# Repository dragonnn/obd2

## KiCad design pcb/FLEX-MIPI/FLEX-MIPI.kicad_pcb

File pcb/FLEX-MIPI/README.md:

# OK-23GF030-04 KiCad library

KiCad symbol, PCB footprint, and simplified STEP model for the 30-pin OCN
`OK-23GF030-04` board-side receptacle. This mates with the
`OK-23GM030-04` plug specified by the Osptek AM319M262928ZS panel drawing.

## Files

- `OK-23GF030-04.kicad_sym` — generic 30-pin connector symbol
- `OK-23GF030-04.pretty/CONN-SMD_30P-OK-23GF030-04.kicad_mod` — 0.4 mm-pitch footprint
- `OK-23GF030-04.3dshapes/CONN-SMD_30P-OK-23GF030-04.step` — simplified STEP model
- `OK-23GF030-04.3dshapes/CONN-SMD_30P-OK-23GF030-04.wrl` — EasyEDA-converted VRML model
- `generate_step.py` — CadQuery source for the STEP model

## Provenance and cautions

The symbol and land pattern were converted from JLCPCB/EasyEDA component
`C9900040133`. The four solder hold-down pads were changed from electrical
pin 0 to unnumbered mechanical pads, and the false pin 0 was removed from
the symbol.

The STEP model is an envelope/placement model aligned to that land pattern.
Its overall envelope is approximately 9.10 x 2.91 x 0.65 mm, including the
solder fittings. It is not manufacturer CAD;
small housing, latch, and mating-interface details are simplified. Confirm
the production footprint, component height, panel engagement, and keep-out
against physical samples or an OCN mechanical drawing before fabrication.

Do not substitute the earlier 24-pin `OK-14F024-04` footprint. It is a
different connector family and pin count.

## KiCad setup

Keep the `ok23_connector` folder at the project root so the footprint's
`${KIPRJMOD}` STEP path resolves. Add `OK-23GF030-04.kicad_sym` through
Preferences -> Manage Symbol Libraries, and add the `.pretty` directory
through Preferences -> Manage Footprint Libraries. Use the nickname
`OK-23GF030-04` for the footprint library.

For JLCPCB assembly, use LCSC/JLCPCB part `C9900040133` and verify current
stock and assembly orientation when ordering.

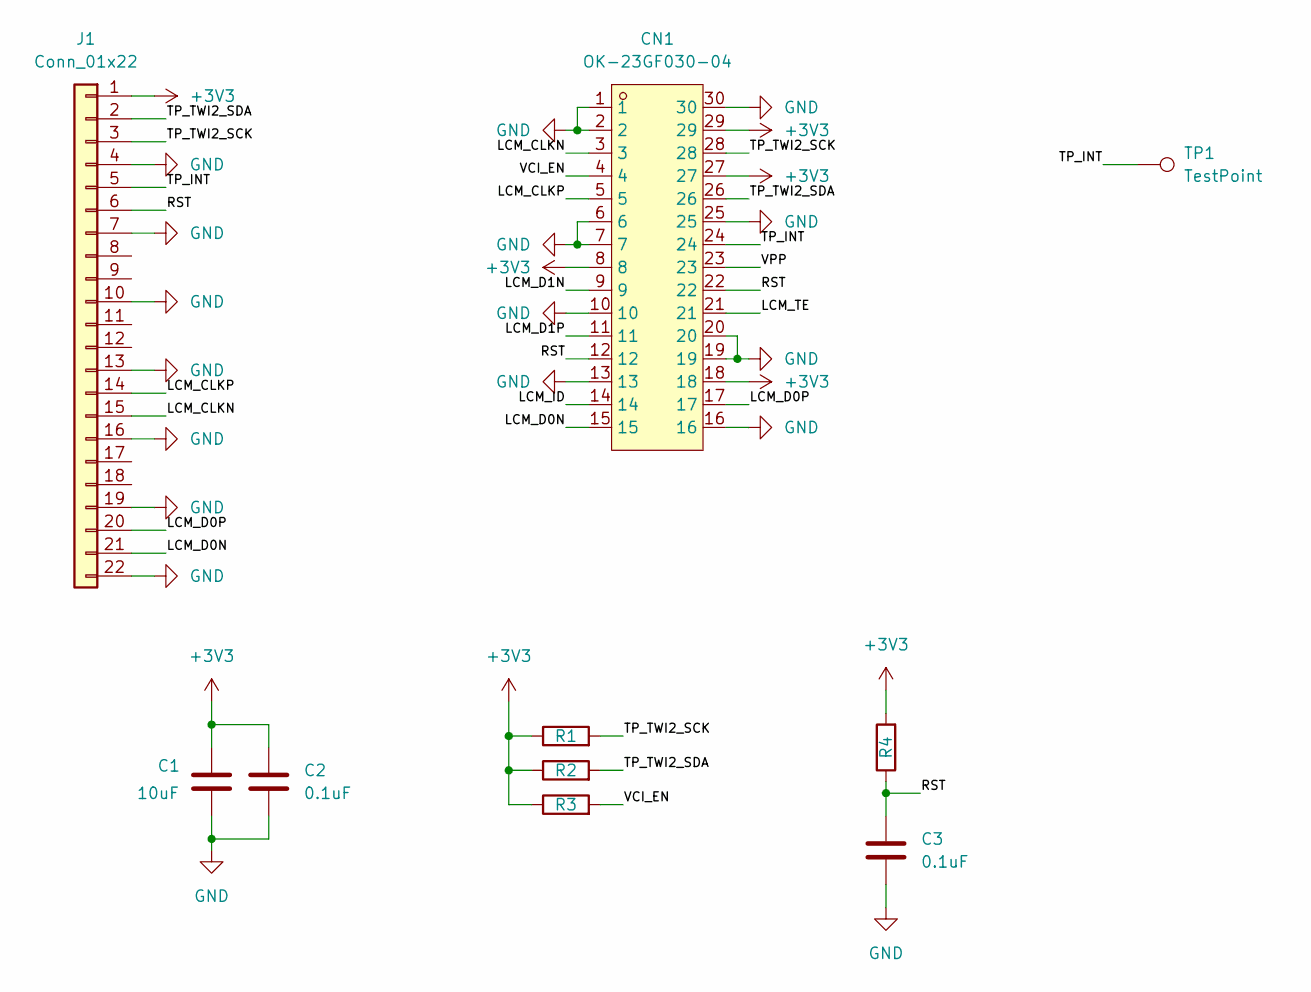
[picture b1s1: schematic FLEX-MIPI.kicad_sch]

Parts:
C1: 10uF; C_0805_2012Metric_Pad1.18x1.45mm_HandSolder
C2, C3: 0.1uF; C_0201_0603Metric_Pad0.64x0.40mm_HandSolder
CN1: OK-23GF030-04; CONN-SMD_30P-OK-23GF030-04; MPN OK-23GF030-04; LCSC Part C9900040133
J1: Conn_01x22; FPC_Tail_22P_P0.5
R1, R2, R3, R4: R; R_0201_0603Metric_Pad0.64x0.40mm_HandSolder
TP1: TestPoint; TestPoint_SMD_1.0x0.6mm_Flex

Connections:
+3V3: C1.1, C2.1, CN1.8, CN1.18, CN1.27, CN1.29, J1.1, R1.1, R2.1, R3.1, R4.2
/LCM_CLKN: CN1.3, J1.15
/LCM_CLKP: CN1.5, J1.14
/LCM_D0N: CN1.15, J1.21
/LCM_D0P: CN1.17, J1.20
/LCM_D1N: CN1.9
/LCM_D1P: CN1.11
/LCM_ID: CN1.14
/LCM_TE: CN1.21
/RST: C3.1, CN1.12, CN1.22, J1.6, R4.1
/TP_INT: CN1.24, J1.5, TP1.1
/TP_TWI2_SCK: CN1.28, J1.3, R1.2
/TP_TWI2_SDA: CN1.26, J1.2, R2.2
/VCI_EN: CN1.4, R3.2
/VPP: CN1.23
GND: C1.2, C2.2, C3.2, CN1.1, CN1.2, CN1.6, CN1.7, CN1.10, CN1.13, CN1.16, CN1.19, CN1.20, CN1.25, CN1.30, J1.4, J1.7, J1.10, J1.13, J1.16, J1.19, J1.22

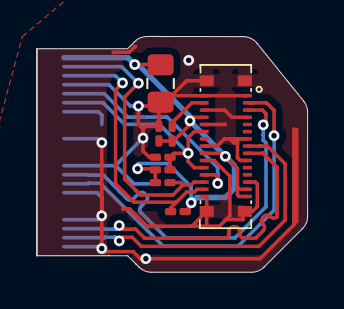
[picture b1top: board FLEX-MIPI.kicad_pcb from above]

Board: 2 copper layers, 15.0 x 13.0 mm, 9 parts (1 on the bottom side), 11 nets.

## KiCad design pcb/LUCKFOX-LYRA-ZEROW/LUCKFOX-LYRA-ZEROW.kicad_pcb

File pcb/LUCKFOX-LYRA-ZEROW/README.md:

# Luckfox Lyra Zero W — KiCad library

Contents:
- `Luckfox_Lyra.kicad_sym` — 40-pin symbol with 5V / 3V3 / GND and RMIO/GPIO names.
- `Luckfox_Lyra.pretty/Luckfox_Lyra_Zero_W_40Pin.kicad_mod` — footprint.
- `Luckfox_Lyra.3dshapes/Luckfox_Lyra_Zero_W.step` — simplified generated STEP model.

## Footprint philosophy
The footprint intentionally has **no F.SilkS board drawing**. The only PCB fabrication geometry is the 2×20 through-hole connector. The SBC board outline, four mounting holes, and mechanical notes are on `Cmts.User` so they are visible while laying out the carrier but do not print on silkscreen.

Board envelope: 65.0 × 30.0 mm. Mounting pattern: 58 × 23 mm, four Ø3.0 mm holes.

The 40-pin expansion connector uses 2.54 mm pitch. Pin 1 is the square pad. Pin numbering follows Raspberry-Pi-style alternating numbering: odd pins on the inner row, even pins on the outer/board-edge row.

## 3D model
Luckfox's documentation repository states that hardware resources include a `Hardware/3D Models/` directory, but an exact official Lyra Zero W STEP file was not available through the public indexed resources used while creating this package. Therefore the included STEP is generated from the published 65 × 30 mm board envelope and mounting geometry. It includes approximate major component envelopes and a generic installed 2×20 header for mechanical visualization. **Do not use component positions/heights from this STEP for a tight enclosure without measuring the real board.**

## Electrical pin mapping
RMIO/GPIO labels were transcribed from the official Luckfox Lyra Zero W schematic.

## Mechanical assumptions
The header and mounting-hole coordinates use the Raspberry Pi Zero-compatible 65 × 30 mm / 58 × 23 mm mechanical convention, consistent with Luckfox's stated Pi-HAT compatibility and published outline. If your carrier has very tight registration requirements, verify pin-1-to-board-edge dimensions against a physical Lyra Zero W before production.

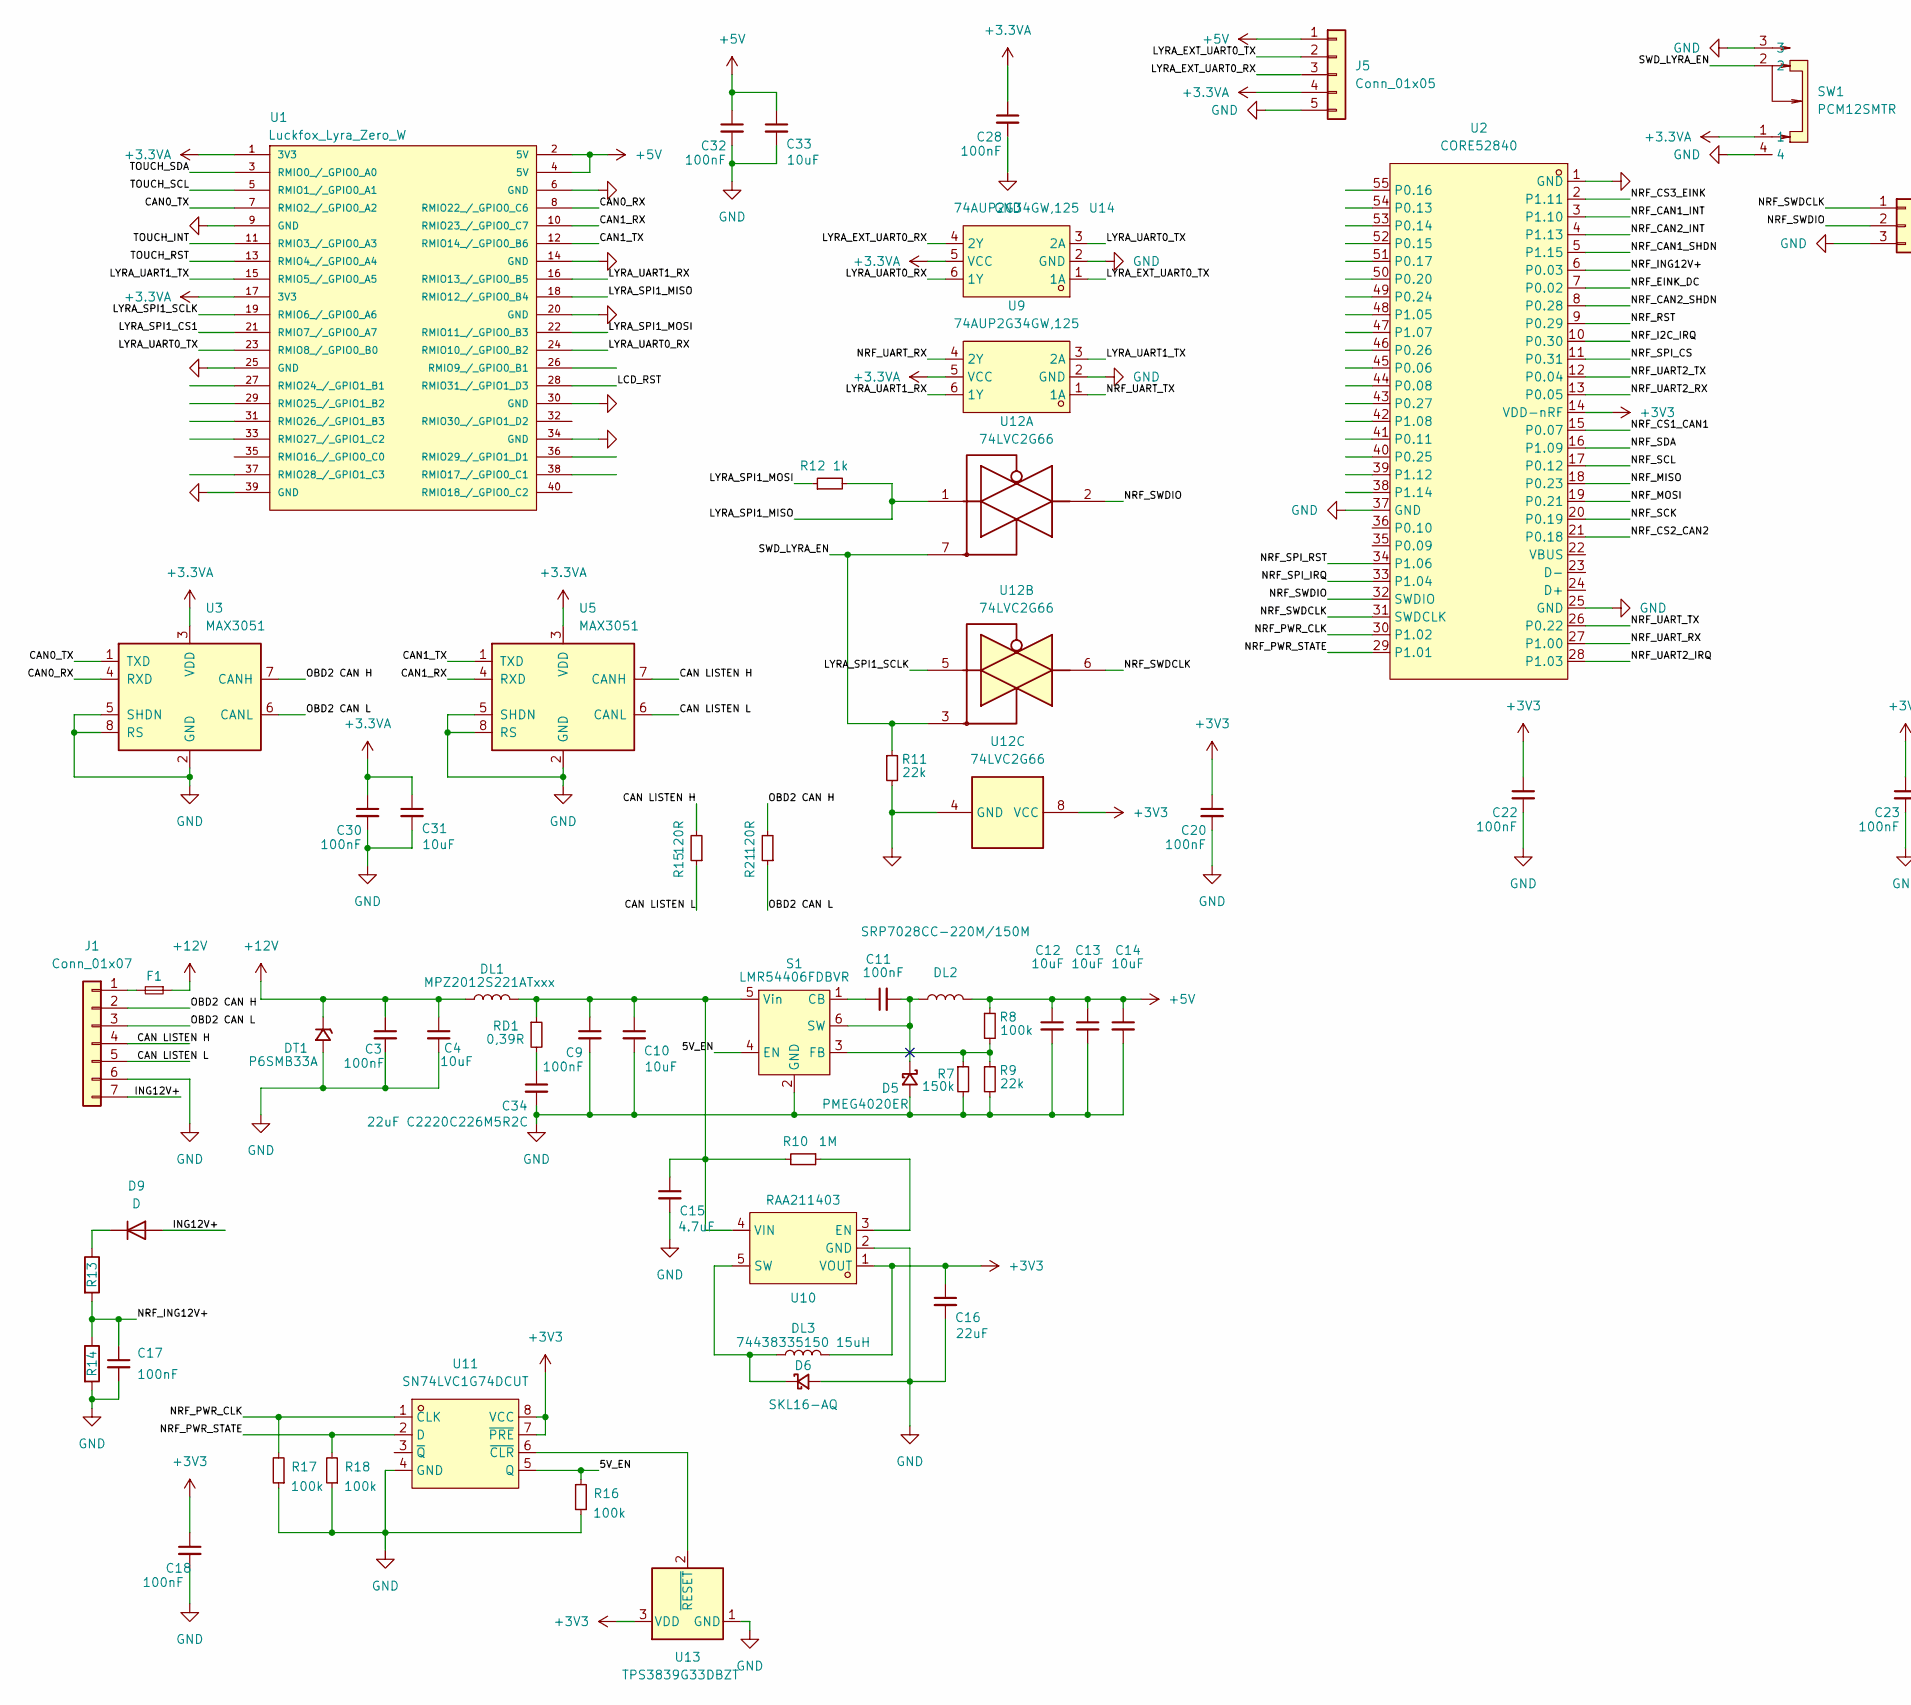
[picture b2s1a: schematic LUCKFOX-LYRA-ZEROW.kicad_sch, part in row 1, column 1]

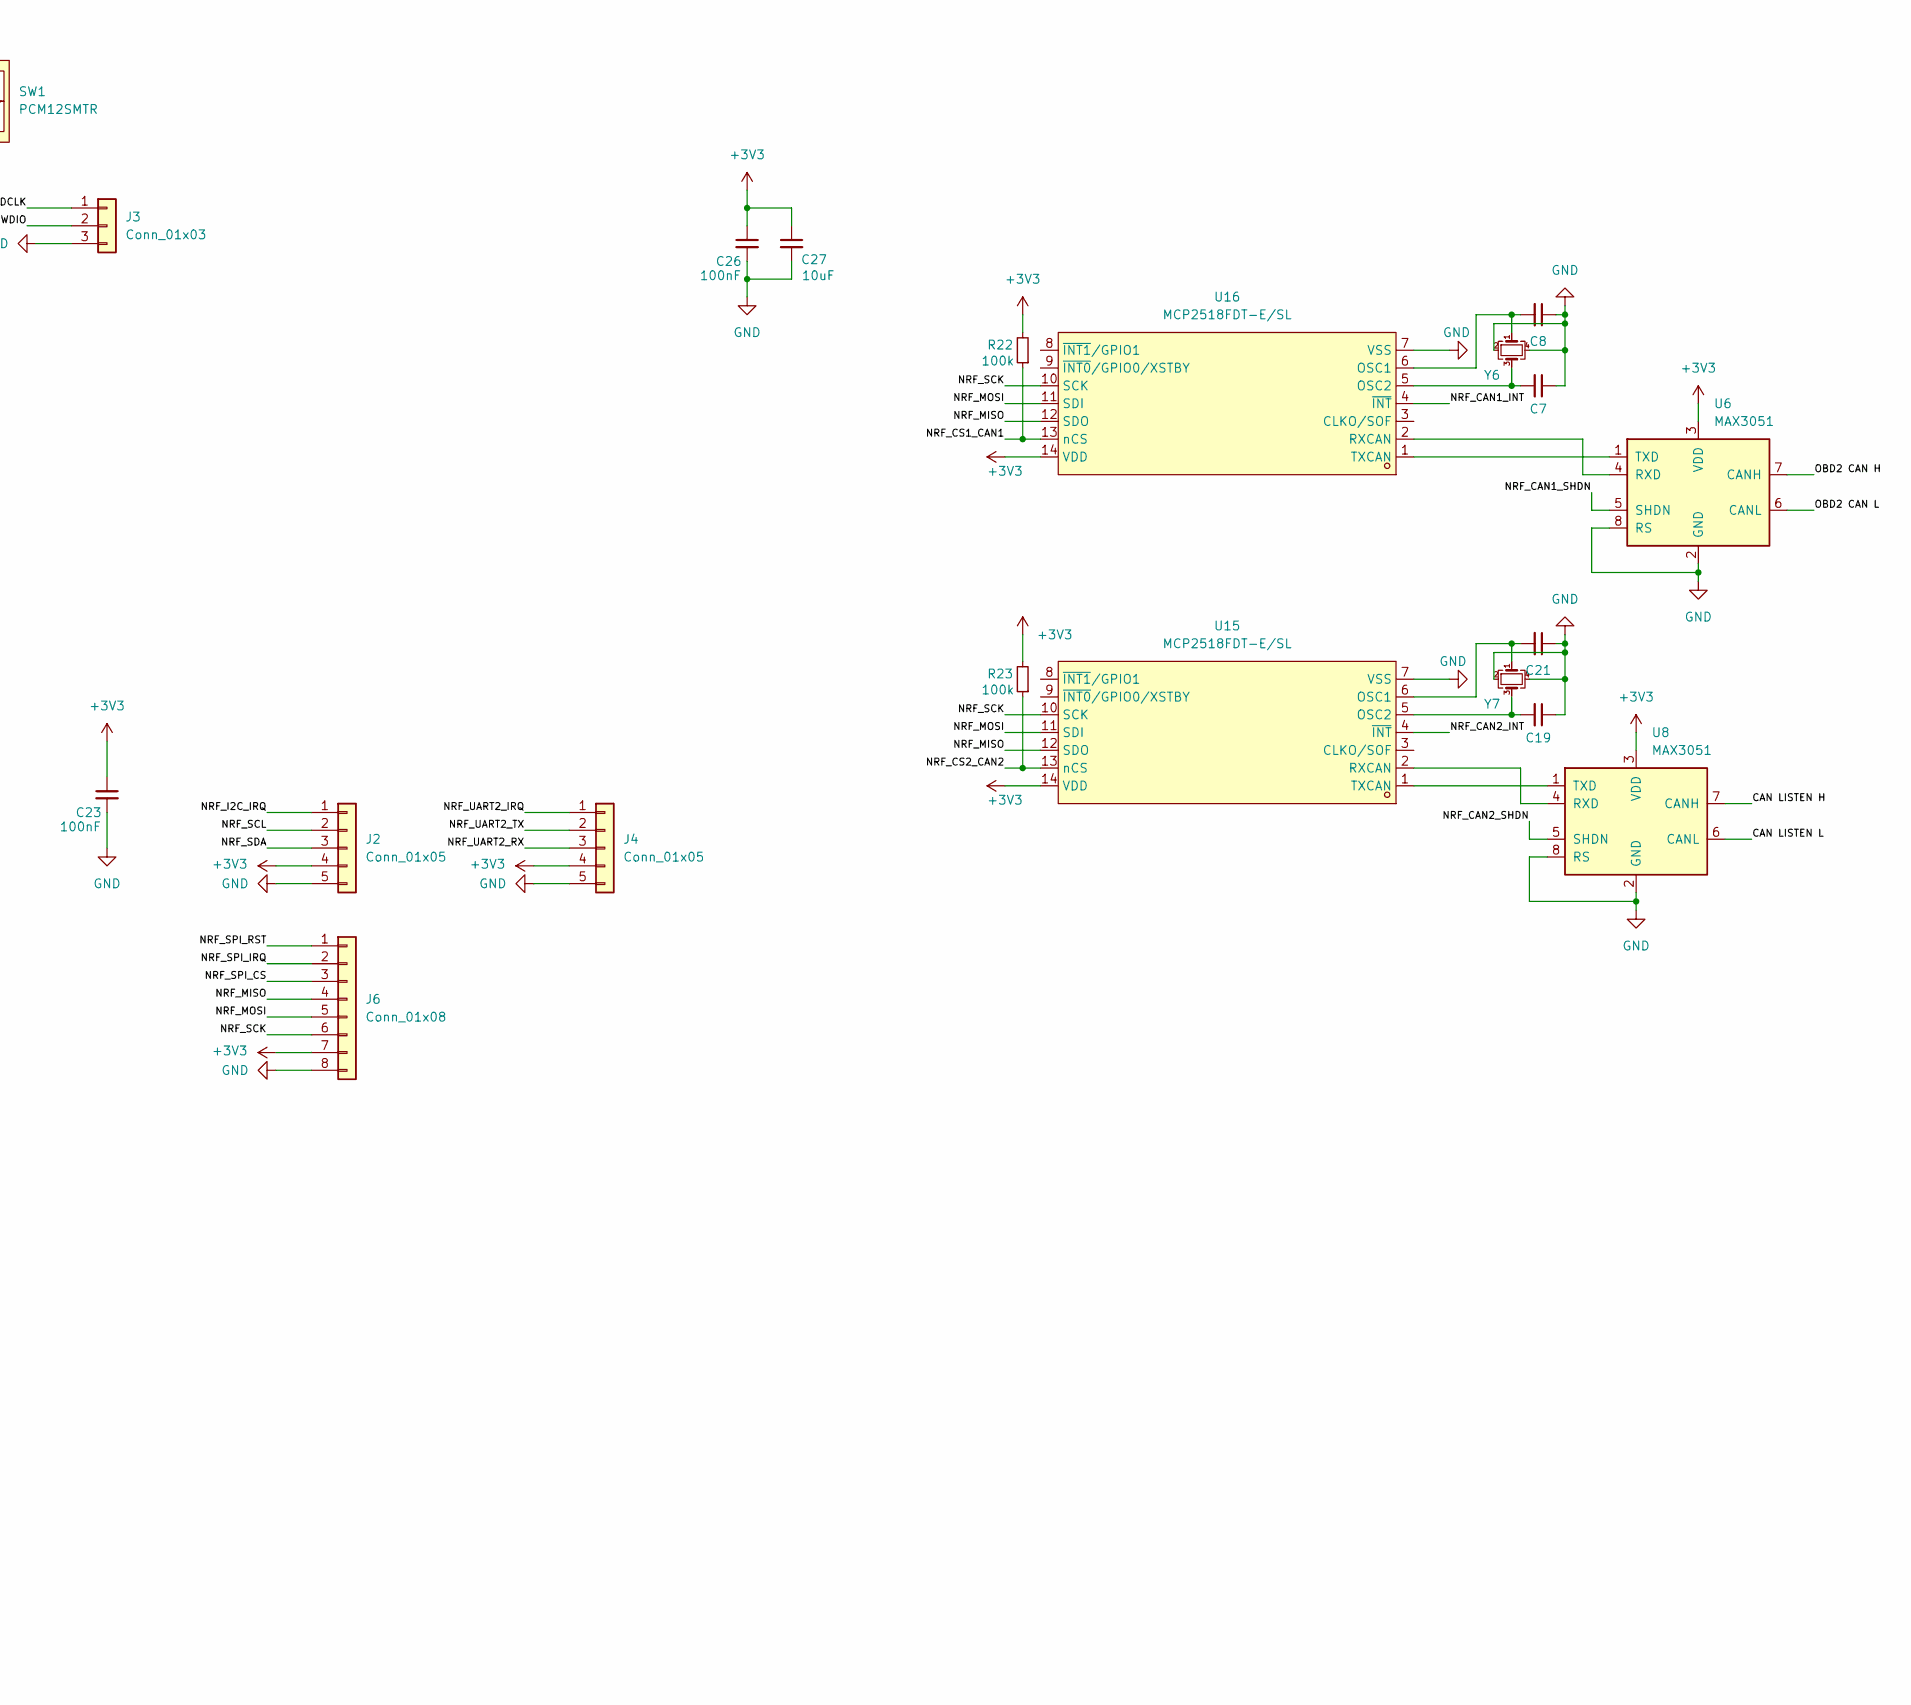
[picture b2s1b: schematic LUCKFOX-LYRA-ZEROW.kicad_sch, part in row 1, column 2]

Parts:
C3, C9, C11, C17, C18, C20, C22, C23, C26, C28, C30, C32: 100nF/50V-X7R_0805; C_0805_2012Metric_Pad1.18x1.45mm_HandSolder
C4, C10, C15, C16, C27, C31, C33: 10uF/50V-X5R(X7R)_1206; C_1206_3216Metric_Pad1.33x1.80mm_HandSolder
C7, C8, C19, C21: 22pF; C_0805_2012Metric
C12, C13, C14: 10uF/16V(25V,35V,50V)-X5R(X7R)_1206; C_1206_3216Metric_Pad1.33x1.80mm_HandSolder
C34: 22uF / 50V; C_2220_5750Metric_Pad1.97x5.40mm_HandSolder
D5: PMEG4020ER; D_SOD-123F
D6: SKL16-AQ; D_SMA_Handsoldering
D9: D; D_0805_2012Metric
DL1: MPZ2012S221ATxxx (MPZ2012S331ATxxx), (BLM21PG221S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; L_0805_2012Metric_Pad1.05x1.20mm_HandSolder
DL2: SRP7028CC-220M/150M; L_Bourns_SRP7028A_7.3x6.6mm
DL3: 15uH; L_Wuerth_MAPI-3015
DT1: P6SMB33A; D_SMB_Handsoldering
F1: Fuse_Small; Fuseholder_Littelfuse_Nano2_154x
J1: Conn_01x07; JST_GH_SM07B-GHS-TB_1x07-1MP_P1.25mm_Horizontal
J2, J4, J5: Conn_01x05; JST_GH_SM05B-GHS-TB_1x05-1MP_P1.25mm_Horizontal
J3: Conn_01x03; JST_GH_SM03B-GHS-TB_1x03-1MP_P1.25mm_Horizontal
J6: Conn_01x08; JST_GH_SM08B-GHS-TB_1x08-1MP_P1.25mm_Horizontal
R7, R10, R16, R17, R18, R22, R23: (150k/1%_0805); R_0805_2012Metric_Pad1.20x1.40mm_HandSolder
R8: 100k/1%_0805; R_0805_2012Metric_Pad1.20x1.40mm_HandSolder
R9, R11: 22k/1%_0805; R_0805_2012Metric_Pad1.20x1.40mm_HandSolder
R12: 1k; R_0805_2012Metric_Pad1.20x1.40mm_HandSolder
R13: 47k; R_0805_2012Metric_Pad1.20x1.40mm_HandSolder
R14: 10k; R_0805_2012Metric_Pad1.20x1.40mm_HandSolder
R15, R21: R_0805_2012Metric_Pad1.20x1.40mm_HandSolder
RD1: 0,39R MMA02040C 3907J(G,F) (0,33R MMA02040C 3307J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; R_MiniMELF_MMA-0204
S1: LMR54406FDBVR (LMR54410FDBVR), (LMR54406DBVR), (L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; SOT-23-6_Handsoldering
SW1: PCM12SMTR; SW-SMD_PCM12SMTR; MPN PCM12SMTR; LCSC Part C221841
U1: Luckfox_Lyra_Zero_W; Luckfox_Lyra_Zero_W_40Pin
U2: CORE52840; BULETM-SMD_HOLYIOT-18010-NRF52840; MPN Core52840; LCSC Part C5374678
U3, U5, U6, U8: MAX3051; SOIC-8_3.9x4.9mm_P1.27mm
U9, U14: 74AUP2G34GW,125; SOT-363_SC-70-6_Handsoldering; MPN 74AUP2G34GW,125; LCSC Part C546130
U10: RAA211403; SOT-23-5_L3.0-W1.7-P0.95-LS2.8-BL; MPN RAA2114034GP3#JA0; LCSC Part C27305571
U11: SN74LVC1G74DCUT; VSSOP-8_2.3x2mm_P0.5mm; MPN SN74LVC1G74DCTR; LCSC Part C840104
U12: 74LVC2G66; TSSOP-8_3x3mm_P0.65mm
U13: TPS3839G33DBZT; SOT-23
U15, U16: MCP2518FDT-E/SL; SOIC-14_L8.7-W3.9-P1.27-LS6.0-BL; MPN MCP2518FDT-E/SL; LCSC Part C626758
Y6, Y7: Crystal_GND24_Small; Crystal_SMD_3225-4Pin_3.2x2.5mm

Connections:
+3.3VA: C28.1, C30.1, C31.1, J5.4, SW1.1, U1.1 (3V3), U1.17 (3V3), U3.3 (VDD), U5.3 (VDD), U9.5 (VCC), U14.5 (VCC)
+3V3: C16.1, C18.1, C20.1, C22.1, C23.1, C26.1, C27.1, DL3.2, J2.4, J4.4, J6.7, R22.2, R23.2, U2.14 (VDD-nRF), U6.3 (VDD), U8.3 (VDD), U10.1 (VOUT), U11.7 (~PRE), U11.8 (VCC), U12.8 (VCC), U13.3 (VDD), U15.14 (VDD), U16.14 (VDD)
+5V: C12.1, C13.1, C14.1, C32.1, C33.1, DL2.2, J5.1, R8.1, U1.2 (5V), U1.4 (5V)
+12V: C3.1, C4.1, DL1.1, DT1.1, F1.1
/5V_EN: R16.2, S1.4 (EN), U11.5 (Q)
/CAN0_RX: U1.8 (RMIO22_/_GPIO0_C6), U3.4 (RXD)
/CAN0_TX: U1.7 (RMIO2_/_GPIO0_A2), U3.1 (TXD)
/CAN1_RX: U1.10 (RMIO23_/_GPIO0_C7), U5.4 (RXD)
/CAN1_TX: U1.12 (RMIO14_/_GPIO0_B6), U5.1 (TXD)
/CAN LISTEN H: J1.4, R15.2, U5.7 (CANH), U8.7 (CANH)
/CAN LISTEN L: J1.5, R15.1, U5.6 (CANL), U8.6 (CANL)
/ING12V+: D9.2 (A), J1.7
/LCD_RST: U1.28 (RMIO31_/_GPIO1_D3)
/LYRA_EXT_UART0_RX: J5.3, U14.4 (2Y)
/LYRA_EXT_UART0_TX: J5.2, U14.1 (1A)
/LYRA_SPI1_CS1: U1.21 (RMIO7_/_GPIO0_A7)
/LYRA_SPI1_MISO: R12.2, U1.18 (RMIO12_/_GPIO0_B4), U12.1
/LYRA_SPI1_MOSI: R12.1, U1.22 (RMIO11_/_GPIO0_B3)
/LYRA_SPI1_SCLK: U1.19 (RMIO6_/_GPIO0_A6), U12.5
/LYRA_UART0_RX: U1.24 (RMIO10_/_GPIO0_B2), U14.6 (1Y)
/LYRA_UART0_TX: U1.23 (RMIO8_/_GPIO0_B0), U14.3 (2A)
/LYRA_UART1_RX: U1.16 (RMIO13_/_GPIO0_B5), U9.6 (1Y)
/LYRA_UART1_TX: U1.15 (RMIO5_/_GPIO0_A5), U9.3 (2A)
/NRF_CAN1_INT: U2.3 (P1.10), U16.4 (~INT)
/NRF_CAN1_SHDN: U2.5 (P1.15), U6.5 (SHDN)
/NRF_CAN2_INT: U2.4 (P1.13), U15.4 (~INT)
/NRF_CAN2_SHDN: U2.8 (P0.28), U8.5 (SHDN)
/NRF_CS1_CAN1: R22.1, U2.15 (P0.07), U16.13 (nCS)
/NRF_CS2_CAN2: R23.1, U2.21 (P0.18), U15.13 (nCS)
/NRF_CS3_EINK: U2.2 (P1.11)
/NRF_EINK_DC: U2.7 (P0.02)
/NRF_I2C_IRQ: J2.1, U2.10 (P0.30)
/NRF_ING12V+: C17.1, R13.2, R14.1, U2.6 (P0.03)
/NRF_MISO: J6.4, U2.18 (P0.23), U15.12 (SDO), U16.12 (SDO)
/NRF_MOSI: J6.5, U2.19 (P0.21), U15.11 (SDI), U16.11 (SDI)
/NRF_PWR_CLK: R17.2, U2.30 (P1.02), U11.1 (CLK)
/NRF_PWR_STATE: R18.2, U2.29 (P1.01), U11.2 (D)
/NRF_RST: U2.9 (P0.29)
/NRF_SCK: J6.6, U2.20 (P0.19), U15.10 (SCK), U16.10 (SCK)
/NRF_SCL: J2.2, U2.17 (P0.12)
/NRF_SDA: J2.3, U2.16 (P1.09)
/NRF_SPI_CS: J6.3, U2.11 (P0.31)
/NRF_SPI_IRQ: J6.2, U2.33 (P1.04)
/NRF_SPI_RST: J6.1, U2.34 (P1.06)
/NRF_SWDCLK: J3.1, U2.31 (SWDCLK), U12.6
/NRF_SWDIO: J3.2, U2.32 (SWDIO), U12.2
/NRF_UART2_IRQ: J4.1, U2.28 (P1.03)
/NRF_UART2_RX: J4.3, U2.13 (P0.05)
/NRF_UART2_TX: J4.2, U2.12 (P0.04)
/NRF_UART_RX: U2.27 (P1.00), U9.4 (2Y)
/NRF_UART_TX: U2.26 (P0.22), U9.1 (1A)
/OBD2 CAN H: J1.2, R21.2, U3.7 (CANH), U6.7 (CANH)
/OBD2 CAN L: J1.3, R21.1, U3.6 (CANL), U6.6 (CANL)
/SWD_LYRA_EN: R11.1, SW1.2, U12.3, U12.7
/TOUCH_INT: U1.11 (RMIO3_/_GPIO0_A3)
/TOUCH_RST: U1.13 (RMIO4_/_GPIO0_A4)
/TOUCH_SCL: U1.5 (RMIO1_/_GPIO0_A1)
/TOUCH_SDA: U1.3 (RMIO0_/_GPIO0_A0)
GND: C3.2, C4.2, C7.1, C8.1, C9.2, C10.2, C12.2, C13.2, C14.2, C15.2, C16.2, C17.2, C18.2, C19.1, C20.2, C21.1, C22.2, C23.2, C26.2, C27.2, C28.2, C30.2, C31.2, C32.2, C33.2, C34.2, D5.2 (A), D6.2 (A), DT1.2, J1.6, J2.5, J3.3, J4.5, J5.5, J6.8, R7.2, R9.2, R11.2, R14.2, R16.1, R17.1, R18.1, S1.2 (GND), SW1.3, SW1.4, U1.6 (GND), U1.9 (GND), U1.14 (GND), U1.20 (GND), U1.25 (GND), U1.30 (GND), U1.34 (GND), U1.39 (GND), U2.1 (GND), U2.25 (GND), U2.37 (GND), U3.2 (GND), U3.5 (SHDN), U3.8 (RS), U5.2 (GND), U5.5 (SHDN), U5.8 (RS), U6.2 (GND), U6.8 (RS), U8.2 (GND), U8.8 (RS), U9.2 (GND), U10.2 (GND), U11.4 (GND), U12.4 (GND), U13.1 (GND), U14.2 (GND), U15.7 (VSS), U16.7 (VSS), Y6.2, Y6.4, Y7.2, Y7.4
unnamed: C34.1, RD1.2
unnamed: C11.2, D5.1 (K), DL2.1, S1.6 (SW)
unnamed: D6.1 (K), DL3.1, U10.5 (SW)
unnamed: D9.1 (K), R13.1
unnamed: F1.2, J1.1
unnamed: C11.1, S1.1 (CB)
unnamed: R7.1, R8.2, R9.1, S1.3 (FB)
unnamed: C9.1, C10.1, C15.1, DL1.2, R10.2, RD1.1, S1.5 (Vin), U10.4 (VIN)
unnamed: R10.1, U10.3 (EN)
unnamed: U11.6 (~CLR), U13.2 (~RESET)
unnamed: C21.2, U15.6 (OSC1), Y7.1
unnamed: C19.2, U15.5 (OSC2), Y7.3
unnamed: U8.4 (RXD), U15.2 (RXCAN)
unnamed: U8.1 (TXD), U15.1 (TXCAN)
unnamed: C8.2, U16.6 (OSC1), Y6.1
unnamed: C7.2, U16.5 (OSC2), Y6.3
unnamed: U6.4 (RXD), U16.2 (RXCAN)
unnamed: U6.1 (TXD), U16.1 (TXCAN)

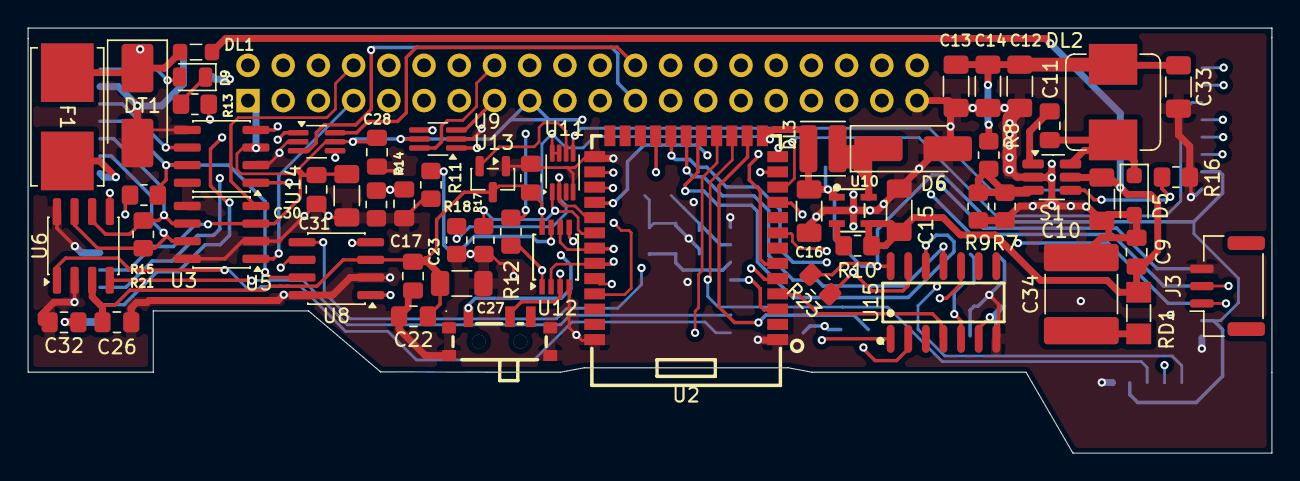
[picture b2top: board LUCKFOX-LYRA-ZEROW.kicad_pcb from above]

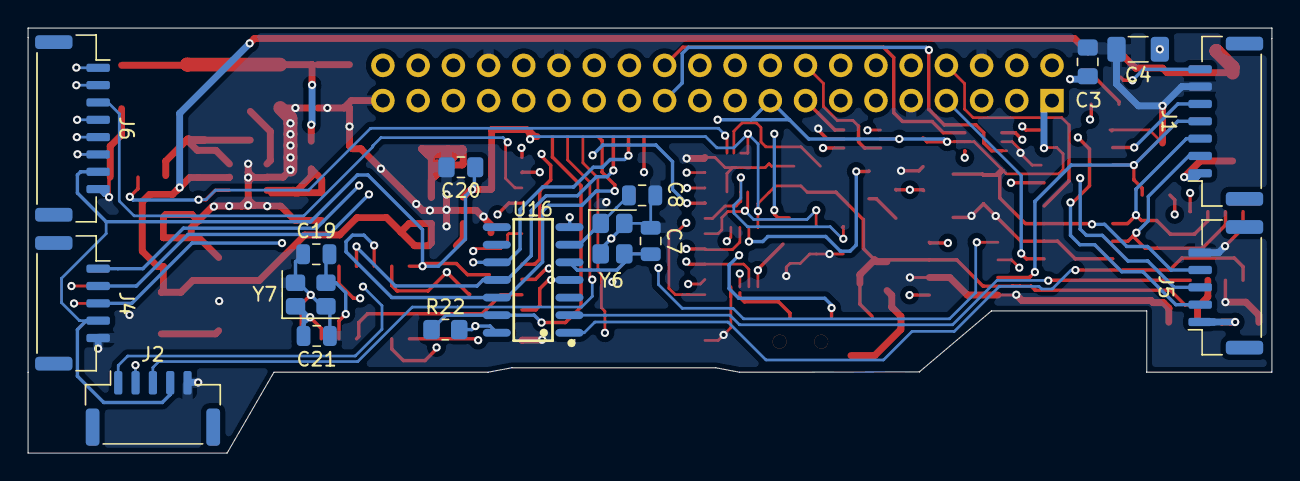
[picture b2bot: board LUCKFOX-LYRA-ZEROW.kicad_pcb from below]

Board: 4 copper layers, 89.7 x 30.7 mm, 75 parts (17 on the bottom side), 68 nets.

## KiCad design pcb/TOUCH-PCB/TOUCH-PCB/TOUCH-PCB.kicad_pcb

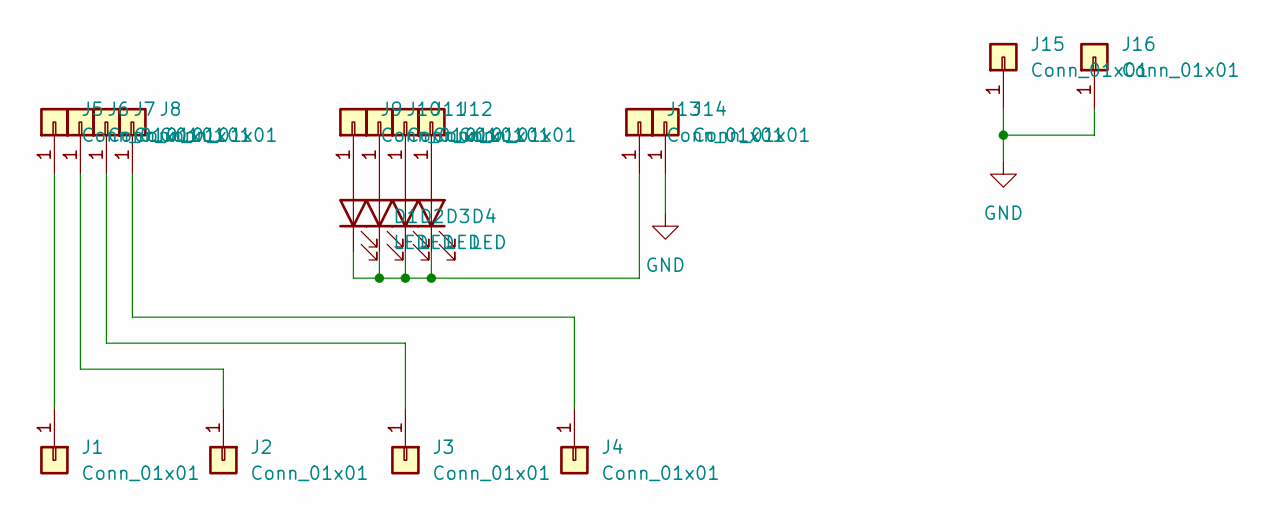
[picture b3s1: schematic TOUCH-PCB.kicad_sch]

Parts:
D1, D2, D3, D4: LED; LED_QBLP617-IW
J1, J2, J3, J4: Conn_01x01; TestPoint_Pad_D4.0mm
J5, J6, J7, J8, J9, J10, J11, J12, J13, J14: Conn_01x01; SolderWirePad_1x01_SMD_1x2mm
J15, J16: Conn_01x01; MountingHole_2.2mm_M2_DIN965_Pad

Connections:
GND: J14.1, J15.1, J16.1
unnamed: D1.2 (A), J9.1
unnamed: D1.1 (K), D2.1 (K), D3.1 (K), D4.1 (K), J13.1
unnamed: D2.2 (A), J10.1
unnamed: D3.2 (A), J11.1
unnamed: D4.2 (A), J12.1
unnamed: J1.1, J5.1
unnamed: J2.1, J6.1
unnamed: J3.1, J7.1
unnamed: J4.1, J8.1

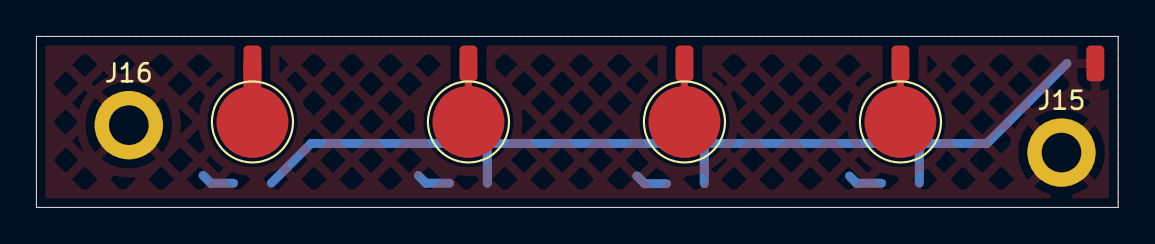
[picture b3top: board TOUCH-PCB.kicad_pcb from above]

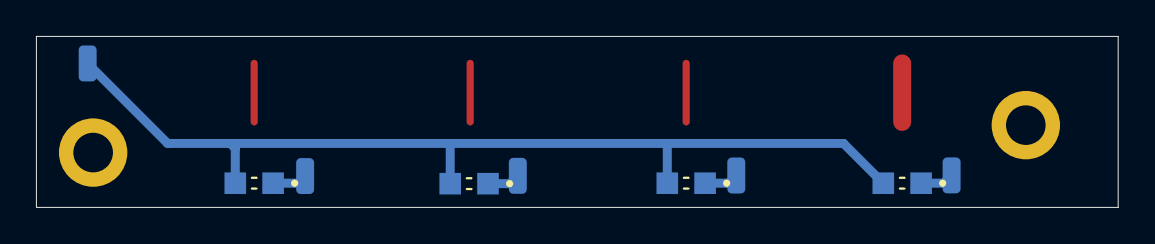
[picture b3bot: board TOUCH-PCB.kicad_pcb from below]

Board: 2 copper layers, 60.1 x 9.5 mm, 20 parts (9 on the bottom side), 10 nets.

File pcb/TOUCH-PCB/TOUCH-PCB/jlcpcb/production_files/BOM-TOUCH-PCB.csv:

Comment,Designator,Footprint,LCSC
Conn_01x01,J15,MountingHole_2.2mm_M2_DIN965_Pad,
Conn_01x01,J14,SolderWirePad_1x01_SMD_1x2mm,
Conn_01x01,J13,SolderWirePad_1x01_SMD_1x2mm,
Conn_01x01,J12,SolderWirePad_1x01_SMD_1x2mm,
Conn_01x01,J11,SolderWirePad_1x01_SMD_1x2mm,
Conn_01x01,J10,SolderWirePad_1x01_SMD_1x2mm,
Conn_01x01,J9,SolderWirePad_1x01_SMD_1x2mm,
Conn_01x01,J8,SolderWirePad_1x01_SMD_1x2mm,
Conn_01x01,J7,SolderWirePad_1x01_SMD_1x2mm,
Conn_01x01,J6,SolderWirePad_1x01_SMD_1x2mm,
Conn_01x01,J5,SolderWirePad_1x01_SMD_1x2mm,
Conn_01x01,J4,TestPoint_Pad_D4.0mm,
Conn_01x01,J3,TestPoint_Pad_D4.0mm,
Conn_01x01,J2,TestPoint_Pad_D4.0mm,
Conn_01x01,J1,TestPoint_Pad_D4.0mm,
LED,D4,LED_QBLP617-IW,
LED,D3,LED_QBLP617-IW,
LED,D2,LED_QBLP617-IW,
LED,D1,LED_QBLP617-IW,
Conn_01x01,J16,MountingHole_2.2mm_M2_DIN965_Pad,
